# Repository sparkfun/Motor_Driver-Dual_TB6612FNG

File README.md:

SparkFun Motor Driver - Dual TB6612FNG (1A)
========================================

<table class="table table-hover table-striped table-bordered">
  <tr align="center">
   <td></td>
   <td></td>
  </tr>
  <tr align="center">
    <td>SparkFun Motor Driver - Dual TB6612FNG (1A) w/out Headers [<a href="https://www.sparkfun.com/products/14451">ROB-14451</a>]</td>
    <td>SparkFun Motor Driver - Dual TB6612FNG with Headers [<a href="https://www.sparkfun.com/products/14450">ROB-14450</a>]</td>
  </tr>
</table>

The TB6612FNG motor driver can control up to two DC motors at a constant current of 1.2A (3.2A peak). Two input signals (IN1 and IN2) can be used to control the motor in one of four function modes - CW, CCW, short-brake, and stop. The two motor outputs (A and B) can be separately controlled, the speed of each motor is controlled via a PWM input signal with a frequency up to 100kHz. The STBY pin should be pulled high to take the motor out of standby mode.

Repository Contents
-------------------

* **/Hardware** - Eagle design files (.brd, .sch)

Documentation
--------------

* **[Hookup Guide](https://learn.sparkfun.com/tutorials/tb6612fng-hookup-guide)** - Basic hookup guide for the TB6612FNG dual motor driver.
* **[SparkFun Fritzing repo](https://github.com/sparkfun/Fritzing_Parts)** - Fritzing diagrams for SparkFun products.
* **[SparkFun 3D Model repo](https://github.com/sparkfun/3D_Models)** - 3D models of SparkFun products. 

Product Versions
----------------
* [ROB-14450](https://www.sparkfun.com/products/14450)- V11 With Headers
* [ROB-14451](https://www.sparkfun.com/products/14451)- V11 Without headers
* *[ROB-13845 (RETIRED)](https://www.sparkfun.com/products/13845)- With Headers*
* *[ROB-09457 (RETIRED)](https://www.sparkfun.com/products/retired/9457)- Without headers*

Version History
---------------
* [v11](https://github.com/sparkfun/Motor_Driver-Dual_TB6612FNG/releases/tag/V_11) - Revision with Silkscreen/Components Update, v11
* [v1.1b](https://github.com/sparkfun/Motor_Driver-Dual_TB6612FNG/releases/tag/V_1.1b) - Minor update
* [v1.1](https://github.com/sparkfun/Motor_Driver-Dual_TB6612FNG/releases/tag/V_1.1) - Initial Release 

License Information
-------------------

This product is _**open source**_! 

Please review the LICENSE.md file for license information. 

If you have any questions or concerns on licensing, please contact techsupport@sparkfun.com.

Distributed as-is; no warranty is given.

- Your friends at SparkFun.

_<COLLABORATION CREDIT>_

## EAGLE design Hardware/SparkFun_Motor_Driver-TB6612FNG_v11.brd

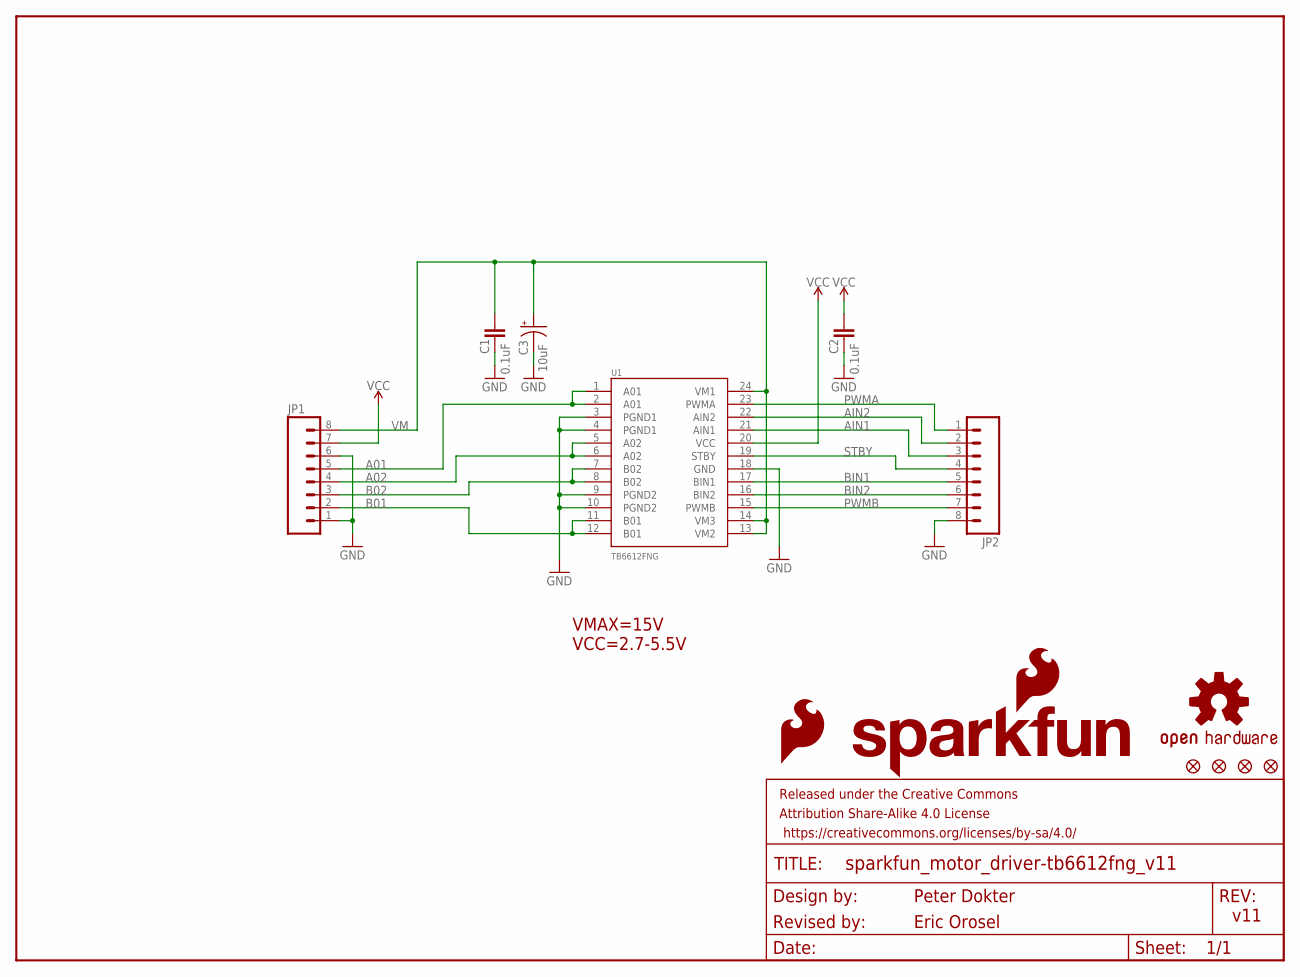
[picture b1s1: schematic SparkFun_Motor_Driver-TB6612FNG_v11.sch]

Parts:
C1, C2: 0.1uF; 0402
C3: 10uF; EIA3528
FD1, FD2, FD3, FD4: FIDUCIALUFIDUCIAL; FIDUCIAL-MICRO
FRAME1: FRAME-LETTER; CREATIVE_COMMONS
JP1, JP2: M0875_PERCENT_REDUCED; 1X08_OFFSET_REDUCED
LOGO1: SFE_LOGO_FLAME.1_INCH; SFE_LOGO_FLAME_.1
LOGO2: OSHW-LOGOS; OSHW-LOGO-S
LOGO4: SFE_LOGO_NAME_FLAME.1_INCH; SFE_LOGO_NAME_FLAME_.1
U1: TB6612FNG; SSOP24

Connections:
A01: JP1.5, U1.1 (A01), U1.2 (A01)
A02: JP1.4, U1.5 (A02), U1.6 (A02)
AIN1: JP2.3, U1.21 (AIN1)
AIN2: JP2.2, U1.22 (AIN2)
B01: JP1.2, U1.11 (B01), U1.12 (B01)
B02: JP1.3, U1.7 (B02), U1.8 (B02)
BIN1: JP2.5, U1.17 (BIN1)
BIN2: JP2.6, U1.16 (BIN2)
GND: C1.2, C2.2, C3.C (-), JP1.1, JP1.6, JP2.8, U1.3 (PGND1), U1.4 (PGND1), U1.9 (PGND2), U1.10 (PGND2), U1.18 (GND)
PWMA: JP2.1, U1.23 (PWMA)
PWMB: JP2.7, U1.15 (PWMB)
STBY: JP2.4, U1.19 (STBY)
VCC: C2.1, JP1.7, U1.20 (VCC)
VM: C1.1, C3.A (+), JP1.8, U1.13 (VM2), U1.14 (VM3), U1.24 (VM1)

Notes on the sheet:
v11
Peter Dokter
Revised by:
Eric Orosel
VMAX=15V VCC=2.7-5.5V

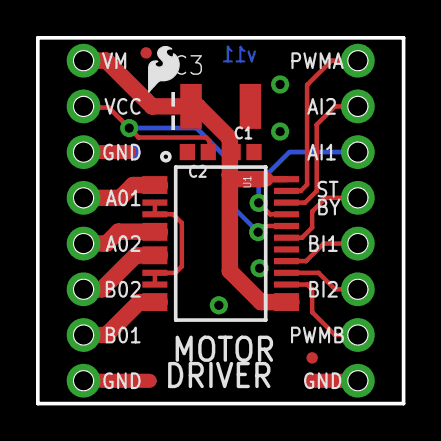
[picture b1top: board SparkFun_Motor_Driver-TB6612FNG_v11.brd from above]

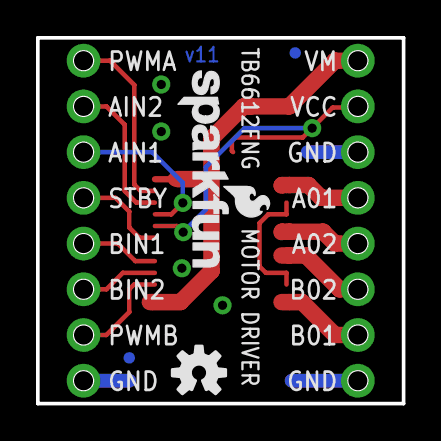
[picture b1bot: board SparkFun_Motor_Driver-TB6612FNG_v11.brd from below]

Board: 2 copper layers, 20.3 x 20.3 mm, 14 parts (4 on the bottom side), 14 nets.

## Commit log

2016-05-12 Initial file commit
2017-08-09 Added v11 TB6612FNG Motor Driver design files
    changes:
    -Moved and added product name silk
    -Added OSHW symbol
    -Pad shape changed to small offset
    -Silk labels added to the top of the board
    -Replace date of design w/ version number
2017-08-09 Changes to design and added 1X08 conn lbr
    -moved and added/removed silk
    -moved fiducials and re routed some traces
    -added new 1X08 offset connector lbr to repo
2017-08-10 Straightened some silk labels
2017-08-10 Changes to SCH and BRD
    -swapped to use micro-fiducials
    -added revised by
    -completed DRC
2017-08-11 changed header
2017-08-11 updated part lbr
2017-08-14 Changed cap parts and added measures
    -Replaced 0603 caps with caps from the sparkfun-capacitors lbr
    -Replaced 10uf cap with cap from the sparkfun-capacitors lbr
    -added measures to the design
2017-08-14 schematic tweaks from double-check
    -gave each VCC pin it's own net and VCC symbol
2018-08-14 Update IC Value
    Regarding this issue [ https://github.com/sparkfun/Motor_Driver-Dual_TB6612FNG/issues/1 ].
    The part used in the board layout and schematic files was incorrectly labeled as TB6621FNG. The value should actually be labeled as TB6612FNG.
2018-08-14 Merge Conflict
    Moving to desktop temporarily.
2018-08-14 Merge Conflict
    Re-adding to v11 branch
2018-08-14 Merge Conflict w/ latest board files
    Files are tagged here if we need to go back => https://github.com/sparkfun/Motor_Driver-Dual_TB6612FNG/releases/tag/V_1.1b
2018-08-14 Create README.md
    Update README.md with new product SKUs.

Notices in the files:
parts and their libraries:
SparkFun-Aesthetics: Licensing: Creative Commons ShareAlike 4.0 International - https://creativecommons.org/licenses/by-sa/4.0
SparkFun-Aesthetics: Released under the Creative Commons Attribution Share-Alike 4.0 License
SparkFun-Aesthetics: https://creativecommons.org/licenses/by-sa/4.0
